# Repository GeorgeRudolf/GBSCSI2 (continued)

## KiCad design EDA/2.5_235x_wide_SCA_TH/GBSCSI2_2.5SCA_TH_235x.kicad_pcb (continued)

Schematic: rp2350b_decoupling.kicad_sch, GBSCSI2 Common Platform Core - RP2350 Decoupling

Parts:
C9, C11, C13, C14, C15, C16, C17, C18, C19, C36, C43: 100nF; C_0402_1005Metric; LCSC C307331
C10: 4.7μF; C_0402_1005Metric; LCSC C23733
C12: 1μF; C_0402_1005Metric; LCSC C52923

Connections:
+1.1V: C9.1, C10.1, C11.1; also elsewhere on the board
+3.3V: C12.1, C13.1, C14.1, C15.1, C16.1, C17.1, C18.1, C19.1, C36.1, C43.1; also elsewhere on the board
GND: C9.2, C10.2, C11.2, C12.2, C13.2, C14.2, C15.2, C16.2, C17.2, C18.2, C19.2, C36.2, C43.2; also elsewhere on the board

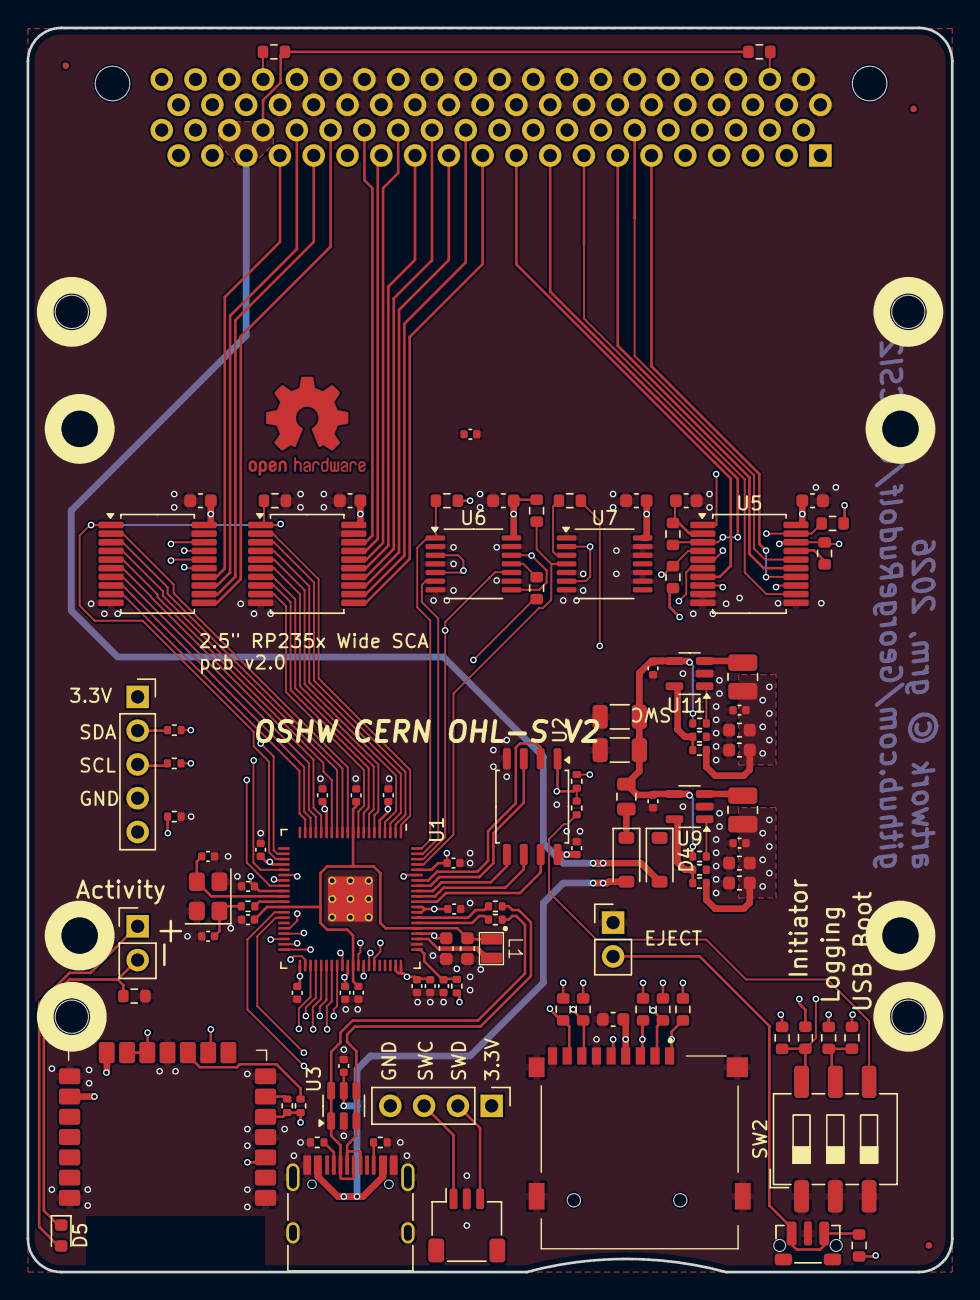
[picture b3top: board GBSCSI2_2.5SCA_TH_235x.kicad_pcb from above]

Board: 4 copper layers, 69.5 x 93.5 mm, 112 parts (1 on the bottom side), 113 nets.

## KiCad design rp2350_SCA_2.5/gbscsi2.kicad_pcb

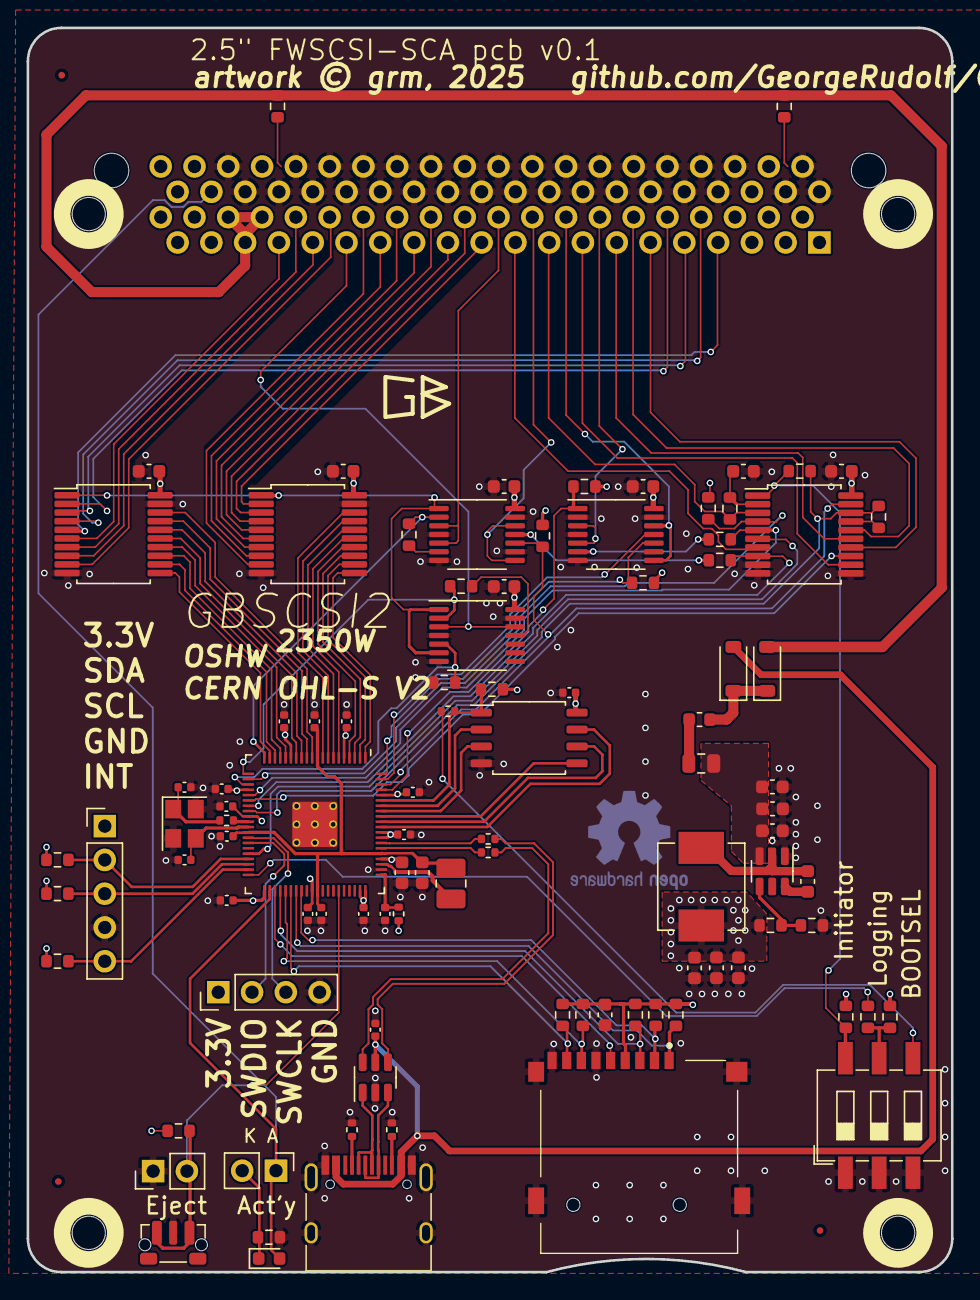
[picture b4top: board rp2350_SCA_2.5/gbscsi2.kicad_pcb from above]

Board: 4 copper layers, 69.5 x 93.6 mm, 105 parts (1 on the bottom side), 113 nets.

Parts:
C1, C15: 10uF; C_0603_1608Metric
C2: 12pF; C_0603_1608Metric
C3, C4, C5, C6, C7, C14, C16, C18, C37: 100nF; C_0603_1608Metric
C12, C13: 22uF; C_0603_1608Metric
C17: 1uF; C_0603_1608Metric
C20, C21: 22pF; C_0402_1005Metric
C22, C24, C27, C28, C29, C30, C31, C32, C33, C34, C38, C39: 100nF; C_0402_1005Metric
C23, C36: 4.7uF; C_0402_1005Metric
C25: 1uF; C_0402_1005Metric
C26, C35: 4.7uF; C_0603_1608Metric
D1: YELLOW; LED_0603_1608Metric
D3, D5: D_Schottky; D_SOD-123
F2: 1A; Fuse_0805_2012Metric
FID1, FID2, FID3: Fiducial; Fiducial_0.5mm_Mask1mm
H1, H2, H3, H4: MH2.5_NPTH
J1: USB_DATA; USB_C_Receptacle_HRO_TYPE-C-31-M-12
J2: TF003; TF01A
J3, J8: Conn_01x02; PinHeader_1x02_P2.54mm_Vertical
J6: Conn_01x05; PinHeader_1x05_P2.54mm_Vertical
J7: Conn_01x04; PinHeader_1x04_P2.54mm_Vertical
J9: Conn_02x40_Counter_Clockwise; CHAMPII_80
L1: Ferrite_Bead_Small; L_0603_1608Metric
L2: 2.2uH; L_Vishay_IHLP-2525
L3: 3.3uH; L_1008_2520Metric_Pad1.43x2.20mm_HandSolder
R1, R2, R3, R5, R7, R8, R9, R10, R11, R12, R13, R15, R40, R51, R52, R54, R66: 4k7; R_0603_1608Metric
R4, R6, R17, R19, R20, R21, R64: 1k; R_0603_1608Metric
R14, R53: 1k; R_0402_1005Metric
R16: 110; R_0603_1608Metric
R18, R42, R67: 10k; R_0603_1608Metric
R41: 31k6; R_0603_1608Metric
R46, R47: 5k1; R_0402_1005Metric
R48, R49, R65: 27; R_0402_1005Metric
R50: 510; R_0603_1608Metric
SW1: SW_DIP_x03; SW_DIP_SPSTx03_Slide_6.7x9.18mm_W8.61mm_P2.54mm_LowProfile
SW2: GT-TC108A-H034-L1S; SW_Push_1P1T-MP_NO_Horizontal_Alps_SKRTLAE010
U1: RP2350_80QFN; RP2350-QFN-80-1EP_10x10_P0.4mm_EP3.4x3.4mm_ThermalVias
U2, U3, U11: 74LVT245; SSOP-20_5.3x7.2mm_P0.65mm
U4, U5, U6: 74LVT125; TSSOP-14_4.4x5mm_P0.65mm
U8: AP62250WU; TSOT-23-6
U9: USB TVS; SOT-23-6
U10: W25Q128JVS; SOIC-8_5.23x5.23mm_P1.27mm
Y1: 12MHz; Crystal_SMD_3225-4Pin_3.2x2.5mm

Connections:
+1V1: C22.1, C23.1, C24.1, C35.1, L3.1, U1.10 (DVDD), U1.32 (DVDD), U1.51 (DVDD), U1.65 (VREG_FB)
+3V3: C1.1, C3.1, C4.1, C5.1, C6.1, C7.1, C12.1, C13.1, C16.1, C25.1, C26.1, C27.1, C28.1, C29.1, C30.1, C31.1, C32.1, C34.1, C37.1, C38.1, C39.1, J2.4 (VDD), J6.1, J7.1, L2.2, R1.2, R2.2, R3.2, R4.1, R5.2, R6.1, R7.2, R11.1, R12.1, R13.1, R15.2, R40.1, R41.1, R51.2, R52.2, R54.2, R65.2, R66.1, U1.5 (IOVDD), U1.15 (IOVDD), U1.24 (IOVDD), U1.29 (IOVDD), U1.41 (IOVDD), U1.50 (IOVDD), U1.59 (ADC_AVDD), U1.60 (IOVDD), U1.64 (VREG_VIN), U1.68 (USB_OTP_VDD), U1.69 (QSPI_IOVDD), U1.76 (IOVDD), U2.20 (VCC), U3.20 (VCC), U4.14 (VCC), U5.14 (VCC), U6.14 (VCC), U10.8 (VCC), U11.20 (VCC)
+5V: C15.1, C17.1, C18.1, F2.2, U8.3 (VIN)
/5V_IN: D3.2 (A), J9.34, J9.35, J9.36, R18.2, R67.2
/5V_TIE: D3.1 (K), D5.1 (K), L1.2
/ACTY: D1.2 (A), J3.1, J9.77, U1.42 (GPIO33)
/ACTY_RTN: D1.1 (K), J3.2, R50.2
/BUS_DIR: R10.2, U1.23 (GPIO23), U4.5
/CC1: J1.A5 (CC1), R47.1
/CC2: J1.B5 (CC2), R46.1
/Din+: J1.A6 (D1+), J1.B6 (D2+), U9.3 (I/O2)
/Din-: J1.A7 (D1-), J1.B7 (D2-), U9.1 (I/O1)
/Dout+: R48.1, U9.4 (I/O2)
/Dout-: R49.1, U9.6 (I/O1)
/EJECT: J8.2, R66.2, SW2.1 (A), U1.55 (GPIO44_ADC4)
/I²C_INT: J6.5, R52.1, U1.39 (GPIO31)
/I²C_SCL: J6.3, R51.1, U1.38 (GPIO30)
/I²C_SDA: J6.2, R15.1, U1.37 (GPIO29)
/QSPI_SCLK: U1.71 (QSPI_SCLK), U10.6 (CLK)
/QSPI_SD0: U1.72 (QSPI_SD0), U10.5 (DI(IO0))
/QSPI_SD1: U1.74 (QSPI_SD1), U10.2 (DO(IO1))
/QSPI_SD2: U1.73 (QSPI_SD2), U10.3 (IO2)
/QSPI_SD3: U1.70 (QSPI_SD3), U10.7 (IO3)
/QSPI_SS: R53.1, R54.1, U1.75 (QSPI_SS), U10.1 (~CS)
/SCSI_I/~O: J9.11, U3.14 (B4)
/SCSI_~ATTN: J9.19, U3.7 (A5)
/SCSI_~C/D: J9.13, U3.15 (B3)
/SCSI_~REQ: J9.12, U3.16 (B2)
/SDIO_CLK: J2.5 (CLK), U1.43 (GPIO34)
/SDIO_CMD: J2.3 (CMD/DI), R3.1, U1.44 (GPIO35)
/SDIO_D0: J2.7 (DAT0/DO), R5.1, U1.45 (GPIO36)
/SDIO_D1: J2.8 (DAT1/NC), R7.1, U1.46 (GPIO37)
/SDIO_D2: J2.1 (DAT2/NC), R1.1, U1.47 (GPIO38)
/SDIO_D3: J2.2 (DAT3/CS), R2.1, U1.48 (GPIO39)
/SWCLK: J7.3, U1.33 (SWCLK)
/SWD: J7.2, U1.34 (SWDIO)
/USB_D+: R48.2, U1.67 (USB_DP)
/USB_D-: R49.2, U1.66 (USB_DM)
/VBUS: C33.1, D5.2 (A), J1.A4 (VBUS), J1.A9 (VBUS), J1.B4 (VBUS), J1.B9 (VBUS), U9.5 (VBUS)
/VREG_LX: L3.2, U1.63 (VREG_LX)
/XIN: R14.1, U1.30 (XIN)
/XOUT: C20.1, U1.31 (XOUT), Y1.3
/~BUS_DIR: U2.1 (A->B), U4.1, U4.6, U5.1, U11.1 (A->B)
/~DEBUG: R9.2, U1.40 (GPIO32)
/~INITIATOR: R4.2, R8.1, SW1.6, U3.1 (A->B)
/~MCU_ACK: R8.2, R17.2, U1.28 (GPIO27), U3.18 (B0)
/~MCU_ATTN: U1.26 (GPIO25), U3.13 (B5)
/~MCU_BSY_OUT: R11.2, U1.78 (GPIO1), U3.19 (CE), U5.10
/~MCU_CD/SEL_IN: R20.1, U1.25 (GPIO24), U3.5 (A3)
/~MCU_IO: U1.36 (GPIO28), U3.6 (A4)
/~MCU_MSG/BSY_IN: R21.1, U1.27 (GPIO26), U3.8 (A6)
/~MCU_REQ: R40.2, U1.22 (GPIO22), U3.4 (A2)
/~MCU_RST_IN: U1.79 (GPIO2), U6.11
/~MCU_RST_OUT: R12.2, U1.80 (GPIO3), U6.10
/~MCU_SD0: U1.1 (GPIO4), U2.11 (B7)
/~MCU_SD1: U1.2 (GPIO5), U2.12 (B6)
/~MCU_SD2: U1.3 (GPIO6), U2.13 (B5)
/~MCU_SD3: U1.4 (GPIO7), U2.14 (B4)
/~MCU_SD4: U1.6 (GPIO8), U2.15 (B3)
/~MCU_SD5: U1.7 (GPIO9), U2.16 (B2)
/~MCU_SD6: U1.8 (GPIO10), U2.17 (B1)
/~MCU_SD7: U1.9 (GPIO11), U2.18 (B0)
/~MCU_SD8: U1.11 (GPIO12), U11.18 (B0)
/~MCU_SD9: U1.12 (GPIO13), U11.17 (B1)
/~MCU_SD10: U1.13 (GPIO14), U11.16 (B2)
/~MCU_SD11: U1.14 (GPIO15), U11.15 (B3)
/~MCU_SD12: U1.16 (GPIO16), U11.14 (B4)
/~MCU_SD13: U1.17 (GPIO17), U11.13 (B5)
/~MCU_SD14: U1.18 (GPIO18), U11.12 (B6)
/~MCU_SD15: U1.19 (GPIO19), U11.11 (B7)
/~MCU_SDP1: R64.2, U1.21 (GPIO21), U4.2
/~MCU_SDP: R19.2, U1.20 (GPIO20), U5.2
/~MCU_SEL_OUT: R13.2, U1.77 (GPIO0), U6.1
/~SCSI_ACK: J9.17, R16.1, U3.3 (A1)
/~SCSI_BSY: J9.18, U5.8, U5.12
/~SCSI_MSG: J9.15, U3.12 (B6)
/~SCSI_RST: J9.16, U6.8, U6.12
/~SCSI_SD0: J9.28, U2.9 (A7)
/~SCSI_SD1: J9.27, U2.8 (A6)
/~SCSI_SD2: J9.26, U2.7 (A5)
/~SCSI_SD3: J9.25, U2.6 (A4)
/~SCSI_SD4: J9.24, U2.5 (A3)
/~SCSI_SD5: J9.23, U2.4 (A2)
/~SCSI_SD6: J9.22, U2.3 (A1)
/~SCSI_SD7: J9.21, U2.2 (A0)
/~SCSI_SD8: J9.10, U11.2 (A0)
/~SCSI_SD9: J9.9, U11.3 (A1)
/~SCSI_SD10: J9.8, U11.4 (A2)
/~SCSI_SD11: J9.7, U11.5 (A3)
/~SCSI_SD12: J9.33, U11.6 (A4)
/~SCSI_SD13: J9.32, U11.7 (A5)
/~SCSI_SD14: J9.31, U11.8 (A6)
/~SCSI_SD15: J9.30, U11.9 (A7)
/~SCSI_SDP1: J9.29, U4.3, U4.12
/~SCSI_SDP: J9.20, U5.3, U5.5
/~SCSI_SEL: J9.14, U6.3, U6.5
/~USB_BOOT: R53.2, SW1.4
GND: C1.2, C2.2, C3.2, C4.2, C5.2, C6.2, C7.2, C12.2, C13.2, C15.2, C16.2, C17.2, C18.2, C20.2, C21.2, C22.2, C23.2, C24.2, C25.2, C26.2, C27.2, C28.2, C29.2, C30.2, C31.2, C32.2, C33.2, C34.2, C35.2, C36.2, C37.2, C38.2, C39.2, J1.A1 (GND), J1.A12 (GND), J1.B1 (GND), J1.B12 (GND), J1.S1 (SHIELD), J2.6 (GND), J2.CD1, J2.MP1, J2.MP2, J2.MP3, J2.MP4, J6.4, J7.4, J8.1, J9.41, J9.42, J9.43, J9.46, J9.47, J9.48, J9.49, J9.50, J9.51, J9.52, J9.53, J9.54, J9.55, J9.56, J9.57, J9.58, J9.59, J9.60, J9.61, J9.62, J9.63, J9.64, J9.65, J9.66, J9.67, J9.68, J9.69, J9.70, J9.71, J9.72, J9.73, J9.75, J9.76, R10.1, R42.2, R46.2, R47.2, R50.1, SW1.1, SW1.2, SW1.3, SW2.2 (B), U1.62 (VREG_PGND), U1.81 (GND), U2.10 (GND), U2.19 (CE), U3.9 (A7), U3.10 (GND), U3.11 (B7), U4.4, U4.7 (GND), U4.13, U5.4, U5.7 (GND), U5.9, U5.13, U6.2, U6.4, U6.7 (GND), U6.9, U6.13, U8.1 (GND), U9.2 (GND), U10.4 (GND), U11.10 (GND), U11.19 (CE), Y1.2, Y1.4
unnamed: C21.1, R14.2, Y1.1
unnamed: F2.1, L1.1
unnamed: J9.44, R67.1
unnamed: J9.74, R18.1
unnamed: R6.2, R9.1, SW1.5
unnamed: R19.1, U5.6
unnamed: R20.2, U6.6
unnamed: R21.2, U5.11
unnamed: R64.1, U4.11
unnamed: C36.1, R65.1, U1.61 (VREG_AVDD)
unnamed: C2.1, R16.2, U3.2 (A0)
unnamed: R17.1, U3.17 (B1)
unnamed: C14.2, U8.6 (BST)
unnamed: R41.2, R42.1, U8.4 (FB)
unnamed: C14.1, L2.1, U8.2 (SW)

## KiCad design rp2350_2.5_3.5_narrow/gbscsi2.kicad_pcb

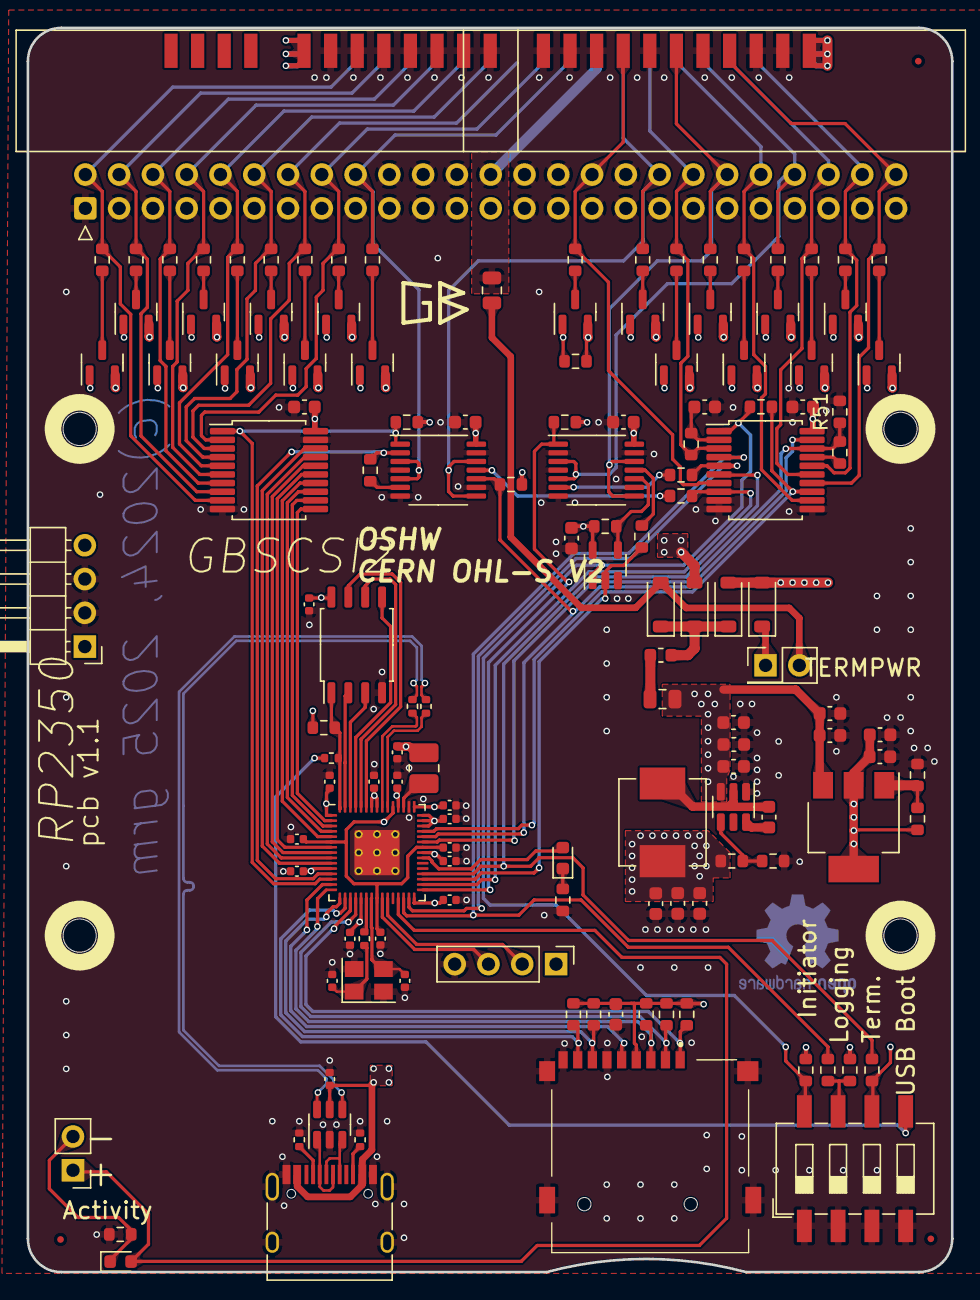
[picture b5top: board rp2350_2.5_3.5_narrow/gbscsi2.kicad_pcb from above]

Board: 4 copper layers, 69.5 x 93.5 mm, 144 parts (0 on the bottom side), 112 nets.

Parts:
C1, C15: 10uF; C_0603_1608Metric
C2: 12pF; C_0603_1608Metric
C3, C4, C5, C6, C7, C10, C11, C14, C16, C18: 100nF; C_0603_1608Metric
C8, C9, C17: 1uF; C_0603_1608Metric
C12, C13: 22uF; C_0603_1608Metric
C20, C21: 22pF; C_0402_1005Metric
C22, C24, C27, C28, C29, C30, C31, C32, C33, C34: 100nF; C_0402_1005Metric
C23, C25: 1uF; C_0402_1005Metric
C26, C35: 4.7uF; C_0402_1005Metric
C36: 100n; C_0402_1005Metric
D1, D6: YELLOW; LED_0603_1608Metric
D2, D3, D4, D5: D_Schottky; D_SOD-123
F1, F2: 1A; Fuse_0805_2012Metric
FID1, FID2, FID3: Fiducial; Fiducial_0.5mm_Mask1mm
H1, H2, H3, H4: MH2.5_NPTH
J1: USB_DATA; USB_C_Receptacle_HRO_TYPE-C-31-M-12
J2: TF003; TF01A
J3: Conn_01x02; PinHeader_1x02_P2.54mm_Vertical
J4: Conn_01x04; PinHeader_1x04_P2.54mm_Horizontal
J5: SCSI_50-2P_2mm; PinHeader_2x25-2_P2.00mm_straddle
J6: SCSI_50P_2.54mm; IDC-Header_2x25_P2.54mm_Horizontal
J7: Conn_01x04; PinHeader_1x04_P2.54mm_Vertical
JP3: Jumper_2_Open; PinHeader_2x01_P2.54mm_Vertical
L1: Ferrite_Bead_Small; L_0603_1608Metric
L2: 2.2uH; L_Vishay_IHLP-2525
L3: 3.3uH; L_1008_2520Metric_Pad1.43x2.20mm_HandSolder
Q1, Q2, Q3, Q4, Q5, Q6, Q7, Q8, Q9, Q10, Q11, Q12, Q13, Q14, Q15, Q16, Q17, Q18: AO3401A; SOT-23
R1, R2, R3, R5, R7, R8, R9, R10, R11, R12, R13, R18, R40, R43, R54: 4k7; R_0603_1608Metric
R4, R6, R17, R19, R20, R21, R51: 1k; R_0603_1608Metric
R14, R53: 1k; R_0402_1005Metric
R16, R22, R23, R24, R25, R26, R27, R28, R29, R30, R31, R32, R33, R34, R35, R36, R37, R38, R39: 110; R_0603_1608Metric
R41: 31k6; R_0603_1608Metric
R42: 10k; R_0603_1608Metric
R44: R_0603_1608Metric
R45: 0; R_0603_1608Metric
R46, R47: 5k1; R_0402_1005Metric
R48, R49: 27; R_0402_1005Metric
R50, R52: 510; R_0603_1608Metric
SW1: SW_DIP_x04; SW_DIP_SPSTx04_Slide_6.7x11.72mm_W8.61mm_P2.54mm_LowProfile
U1: RP2350_60QFN; RP2350-QFN-60-1EP_7x7_P0.4mm_EP3.4x3.4mm_ThermalVias
U2, U3: 74LVT245; SSOP-20_5.3x7.2mm_P0.65mm
U4: 74AHCT1G125; SOT-23-5
U5, U6: 74LVT125; TSSOP-14_4.4x5mm_P0.65mm
U7: AZ1117-2.85; SOT-223-3_TabPin2
U8: AP62250WU; TSOT-23-6
U9: USB TVS; SOT-23-6
U10: W25Q128JVS; SOIC-8_5.23x5.23mm_P1.27mm
Y1: 12MHz; Crystal_SMD_3225-4Pin_3.2x2.5mm

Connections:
+1V1: C22.1, C23.1, C24.1, C35.1, L3.1, U1.6 (DVDD), U1.23 (DVDD), U1.39 (DVDD), U1.50 (VREG_FB)
+2V8: C9.1, C11.1, Q1.2 (S), Q2.2 (S), Q3.2 (S), Q4.2 (S), Q5.2 (S), Q6.2 (S), Q7.2 (S), Q8.2 (S), Q9.2 (S), Q10.2 (S), Q11.2 (S), Q12.2 (S), Q13.2 (S), Q14.2 (S), Q15.2 (S), Q16.2 (S), Q17.2 (S), Q18.2 (S), R40.1, R44.2, U7.2 (VO)
+3V3: C1.1, C3.1, C4.1, C5.1, C6.1, C7.1, C12.1, C13.1, C16.1, C25.1, C26.1, C27.1, C28.1, C29.1, C30.1, C31.1, C32.1, C34.1, C36.1, J2.4 (VDD), J7.1, L2.2, R1.2, R2.2, R3.2, R4.1, R5.2, R6.1, R7.2, R10.1, R11.1, R12.1, R13.1, R41.1, R54.2, U1.1 (IOVDD), U1.11 (IOVDD), U1.20 (IOVDD), U1.30 (IOVDD), U1.38 (IOVDD), U1.43 (GPIO29_ADC3), U1.44 (ADC_AVDD), U1.45 (IOVDD), U1.46 (VREG_AVDD), U1.49 (VREG_VIN), U1.53 (USB_OTP_VDD), U1.54 (QSPI_IOVDD), U2.20 (VCC), U3.20 (VCC), U4.5 (VCC), U5.14 (VCC), U6.14 (VCC), U10.8 (VCC)
+5V: C8.1, C10.1, C15.1, C17.1, C18.1, F2.2, U7.3 (VI), U8.3 (VIN)
/5V_IN: D2.2 (A), D3.2 (A), J4.1, J5.1, J5.2, J5.39, J5.40
/5V_TIE: D3.1 (K), D4.1 (K), D5.1 (K), L1.2
/ACTY: D1.1 (K), J3.2, R50.2
/CC1: J1.A5 (CC1), R47.1
/CC2: J1.B5 (CC2), R46.1
/Din+: J1.A6 (D1+), J1.B6 (D2+), U9.3 (I/O2)
/Din-: J1.A7 (D1-), J1.B7 (D2-), U9.1 (I/O1)
/Dout+: R48.1, U9.4 (I/O2)
/Dout-: R49.1, U9.6 (I/O1)
/GPIO16: D1.2 (A), J3.1, U1.27 (GPIO16)
/MCU_RST: R18.2, U1.33 (GPIO21), U4.2
/QSPI_SCLK: U1.56 (QSPI_SCLK), U10.6 (CLK)
/QSPI_SD0: U1.57 (QSPI_SD0), U10.5 (DI(IO0))
/QSPI_SD1: U1.59 (QSPI_SD1), U10.2 (DO(IO1))
/QSPI_SD2: U1.58 (QSPI_SD2), U10.3 (IO2)
/QSPI_SD3: U1.55 (QSPI_SD3), U10.7 (IO3)
/QSPI_SS: R53.1, R54.1, U1.60 (QSPI_SS), U10.1 (~CS)
/SCSI_I/~O: J5.33, J6.50, R39.1, U3.14 (B4)
/SCSI_~ATTN: J5.25, J6.32, R31.1, U3.7 (A5)
/SCSI_~C/D: J5.34, J6.46, R37.1, U3.15 (B3)
/SCSI_~REQ: J5.36, J6.48, R38.1, U3.16 (B2)
/SDIO_CLK: J2.5 (CLK), U1.14 (GPIO10)
/SDIO_CMD: J2.3 (CMD/DI), R3.1, U1.15 (GPIO11)
/SDIO_D0: J2.7 (DAT0/DO), R5.1, U1.16 (GPIO12)
/SDIO_D1: J2.8 (DAT1/NC), R7.1, U1.17 (GPIO13)
/SDIO_D2: J2.1 (DAT2/NC), R1.1, U1.18 (GPIO14)
/SDIO_D3: J2.2 (DAT3/CS), R2.1, U1.19 (GPIO15)
/SWCLK: J7.3, U1.24 (SWCLK)
/SWD: J7.2, U1.25 (SWD)
/TERMPWR: F1.1, J5.24, J6.26
/USB_D+: R48.2, U1.52 (USB_DP)
/USB_D-: R49.2, U1.51 (USB_DM)
/VBUS: C33.1, D5.2 (A), J1.A4 (VBUS), J1.A9 (VBUS), J1.B4 (VBUS), J1.B9 (VBUS), U9.5 (VBUS)
/VREG_LX: L3.2, U1.48 (VREG_LX)
/XIN: R14.1, U1.21 (XIN)
/XOUT: C20.1, U1.22 (XOUT), Y1.3
/~BUS_DIR: R10.2, U1.13 (GPIO9), U2.1 (A->B), U5.1
/~DEBUG: R6.2, R9.1, SW1.7
/~INITIATOR: R4.2, R8.1, SW1.8, U3.1 (A->B), U4.1
/~MCU_ACK: R17.2, R51.1, U1.40 (GPIO26_ADC0), U3.18 (B0)
/~MCU_ATTN: R8.2, U1.42 (GPIO28_ADC2), U3.13 (B5)
/~MCU_BSY_OUT: R11.2, U1.41 (GPIO27_ADC1), U3.19 (CE), U5.10
/~MCU_CD/SEL_IN: R20.1, U1.29 (GPIO18), U3.5 (A3)
/~MCU_IO: R43.2, U1.34 (GPIO22), U3.6 (A4)
/~MCU_MSG/BSY_IN: R21.1, U1.32 (GPIO20), U3.8 (A6)
/~MCU_REQ: R9.2, U1.28 (GPIO17), U3.4 (A2)
/~MCU_SD0: U1.2 (GPIO0), U2.11 (B7)
/~MCU_SD1: U1.3 (GPIO1), U2.12 (B6)
/~MCU_SD2: U1.4 (GPIO2), U2.13 (B5)
/~MCU_SD3: U1.5 (GPIO3), U2.14 (B4)
/~MCU_SD4: U1.7 (GPIO4), U2.15 (B3)
/~MCU_SD5: U1.8 (GPIO5), U2.16 (B2)
/~MCU_SD6: U1.9 (GPIO6), U2.17 (B1)
/~MCU_SD7: U1.10 (GPIO7), U2.18 (B0)
/~MCU_SDP: R19.2, U1.12 (GPIO8), U5.2
/~MCU_SEL_OUT: R13.2, U1.31 (GPIO19), U6.1
/~RST_OUT: R12.2, U4.4, U6.10
/~SCSI_ACK: J5.28, J6.38, R16.1, R33.1, U3.3 (A1)
/~SCSI_BSY: J5.26, J6.36, R32.1, U5.8, U5.12
/~SCSI_MSG: J5.30, J6.42, R35.1, U3.12 (B6)
/~SCSI_RST: J5.29, J6.40, R34.1, U6.8, U6.12
/~SCSI_SD0: J5.6, J6.2, R22.1, U2.9 (A7)
/~SCSI_SD1: J5.8, J6.4, R23.1, U2.8 (A6)
/~SCSI_SD2: J5.10, J6.6, R24.1, U2.7 (A5)
/~SCSI_SD3: J5.12, J6.8, R25.1, U2.6 (A4)
/~SCSI_SD4: J5.14, J6.10, R26.1, U2.5 (A3)
/~SCSI_SD5: J5.16, J6.12, R27.1, U2.4 (A2)
/~SCSI_SD6: J5.18, J6.14, R28.1, U2.3 (A1)
/~SCSI_SD7: J5.20, J6.16, R29.1, U2.2 (A0)
/~SCSI_SDP: J5.22, J6.18, R30.1, U5.3, U5.5
/~SCSI_SEL: J5.32, J6.44, R36.1, U6.3, U6.5
/~TERM_EN: Q1.1 (G), Q2.1 (G), Q3.1 (G), Q4.1 (G), Q5.1 (G), Q6.1 (G), Q7.1 (G), Q8.1 (G), Q9.1 (G), Q10.1 (G), Q11.1 (G), Q12.1 (G), Q13.1 (G), Q14.1 (G), Q15.1 (G), Q16.1 (G), Q17.1 (G), Q18.1 (G), R40.2, R43.1, SW1.6
/~USB_BOOT: R53.2, SW1.5
GND: C1.2, C2.2, C3.2, C4.2, C5.2, C6.2, C7.2, C8.2, C9.2, C10.2, C11.2, C12.2, C13.2, C15.2, C16.2, C17.2, C18.2, C20.2, C21.2, C22.2, C23.2, C24.2, C25.2, C26.2, C27.2, C28.2, C29.2, C30.2, C31.2, C32.2, C33.2, C34.2, C35.2, C36.2, J1.A1 (GND), J1.A12 (GND), J1.B1 (GND), J1.B12 (GND), J1.S1 (SHIELD), J2.6 (GND), J2.CD1, J2.MP1, J2.MP2, J2.MP3, J2.MP4, J4.2, J4.3, J5.3, J5.4, J5.5, J5.7, J5.9, J5.11, J5.13, J5.15, J5.19, J5.21, J5.23, J5.27, J5.31, J5.35, J5.37, J5.38, J6.1, J6.3, J6.5, J6.7, J6.9, J6.11, J6.13, J6.15, J6.17, J6.19, J6.20, J6.21, J6.22, J6.23, J6.24, J6.25, J6.27, J6.28, J6.29, J6.30, J6.31, J6.33, J6.34, J6.35, J6.37, J6.39, J6.41, J6.43, J6.45, J6.47, J6.49, J7.4, R42.2, R45.1, R46.2, R47.2, R50.1, R51.2, R52.1, SW1.1, SW1.2, SW1.3, SW1.4, U1.47 (VREG_PGND), U1.61 (GND), U2.10 (GND), U2.19 (CE), U3.9 (A7), U3.10 (GND), U3.11 (B7), U4.3 (GND), U5.4, U5.7 (GND), U5.9, U5.13, U6.2, U6.4, U6.7 (GND), U6.9, U6.13, U8.1 (GND), U9.2 (GND), U10.4 (GND), Y1.2, Y1.4
unnamed: C21.1, R14.2, Y1.1
unnamed: D2.1 (K), JP3.1 (A)
unnamed: D4.2 (A), F1.2, JP3.2 (B)
unnamed: D6.2 (A), U1.37 (GPIO25)
unnamed: D6.1 (K), R52.2
unnamed: F2.1, L1.1
unnamed: Q1.3 (D), R22.2
unnamed: Q2.3 (D), R23.2
unnamed: Q3.3 (D), R24.2
unnamed: Q4.3 (D), R25.2
unnamed: Q5.3 (D), R26.2
unnamed: Q6.3 (D), R27.2
unnamed: Q7.3 (D), R28.2
unnamed: Q8.3 (D), R29.2
unnamed: Q9.3 (D), R30.2
unnamed: Q10.3 (D), R31.2
unnamed: Q11.3 (D), R32.2
unnamed: Q12.3 (D), R33.2
unnamed: Q13.3 (D), R34.2
unnamed: Q14.3 (D), R35.2
unnamed: Q15.3 (D), R36.2
unnamed: Q16.3 (D), R37.2
unnamed: Q17.3 (D), R38.2
unnamed: Q18.3 (D), R39.2
unnamed: R18.1, U6.11
unnamed: R19.1, U5.6
unnamed: R20.2, U6.6
unnamed: R21.2, U5.11
unnamed: C2.1, R16.2, U3.2 (A0)
unnamed: R17.1, U3.17 (B1)
unnamed: R44.1, R45.2, U7.1 (GND)
unnamed: C14.2, U8.6 (BST)
unnamed: R41.2, R42.1, U8.4 (FB)
unnamed: C14.1, L2.1, U8.2 (SW)

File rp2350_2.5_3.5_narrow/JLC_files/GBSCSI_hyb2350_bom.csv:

Designator,Footprint,Quantity,Value,LCSC Part #
"C1, C10, C11, C14, C16, C18, C3, C4, C5, C6, C7",603,11,100nF,C14663
"C12, C13",603,2,22uF,C59461
C15,603,1,10uF,C96446
"C17, C8, C9",603,3,1uF,C15849
C2,603,1,12pF,C38523
"C20, C21",402,2,22pF,C1555
"C22, C24, C27, C28, C29, C30, C31, C32, C33, C34",402,10,100nF,C307331
"C23, C25",402,2,1uF,C52923
"C26, C35",402,2,4.7uF,
C36,402,1,100n,
"D1, D6",603,2,YELLOW,C72038
"D2, D3, D4, D5",D_SOD-123,4,D_Schottky,C82544
"F1, F2",805,2,1A,C468888
FID1,Fiducial_0.5mm_Mask1mm,1,Fiducial,N/A
J1,USB_C_Receptacle_HRO_TYPE-C-31-M-12,1,USB_DATA,C165948
J2,TF01A,1,TF003,C5155563 
J3,PinHeader_1x02_P2.54mm_Vertical,1,Conn_01x02,N/A
J4,PinHeader_1x04_P2.54mm_Horizontal,1,Conn_01x04,N/A
J5,PinHeader_2x25-2_P2.00mm_straddle,1,SCSI_50-2P_2mm,N/A
J6,IDC-Header_2x25_P2.54mm_Horizontal,1,SCSI_50P_2.54mm,N/A
J7,PinHeader_1x04_P2.54mm_Vertical,1,Conn_01x04,N/A
JP3,PinHeader_2x01_P2.54mm_Vertical,1,Jumper_2_Open,N/A
L1,603,1,Ferrite_Bead_Small,C1002
L2,L_Vishay_IHLP-2525,1,2.2uH,C540967
L3,1008,1,3.3uH,C222831
"Q1, Q10, Q11, Q12, Q13, Q14, Q15, Q16, Q17, Q18, Q2, Q3, Q4, Q5, Q6, Q7, Q8, Q9",SOT-23,18,AO3401A,C15127
"R1, R10, R11, R12, R13, R18, R2, R3, R40, R43, R5, R54, R7, R8, R9",603,15,4k7,C23162
"R14, R53",402,2,1k,C11702
"R16, R22, R23, R24, R25, R26, R27, R28, R29, R30, R31, R32, R33, R34, R35, R36, R37, R38, R39",603,19,110,C22781
"R17, R19, R20, R21, R4, R51, R6",603,7,1k,C21190
R41,603,1,31k6,C25967
R42,603,1,10k,C25804
R45,603,1,0,C21189
"R46, R47",402,2,5k1,C25905
"R48, R49",402,2,27,C25092
"R50, R52",603,2,510,C23193
SW1,SW_DIP_SPSTx04_Slide_6.7x11.72mm_W8.61mm_P2.54mm_LowProfile,1,SW_DIP_x04,C5160841
U1,RP2350-QFN-60-1EP_7x7_P0.4mm_EP3.4x3.4mm_ThermalVias,1,RP2350_60QFN,C9900136995
U10,SOIC-8_5.23x5.23mm_P1.27mm,1,W25Q128JVS,C97521
"U2, U3",SSOP-20_5.3x7.2mm_P0.65mm,2,74LVT245,C2652121
U4,SOT-23-5,1,74AHCT1G125,C12494
"U5, U6",TSSOP-14_4.4x5mm_P0.65mm,2,74LVT125,C7042
U7,SOT-223-3_TabPin2,1,AZ1117-2.85,C14791
U8,TSOT-23-6,1,AP62250WU,C5184228
U9,SOT-23-6,1,USB TVS,C2827654
Y1,Crystal_SMD_3225-4Pin_3.2x2.5mm,1,12MHz,C133334

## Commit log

2024-03-27 Initial file addition
2024-03-27 Added instructions
2024-04-06 Added Pico populating info
2024-04-23 Corrected wrong keying on 2.5" connector
2024-04-23 Update README.md
    After much fumbling, it's finally right.
2024-08-08 added WIP RP2350 variant
2024-08-30 Changed diodes in BoM, minor corrections to PCB, documentation
2024-10-04 BoM fixes for discrete variants, interactive BoMs added to each major type, mfg files for 2350
2024-10-04 Corrected U9 rotation
2024-10-27 moving RP2350 to full release
2024-10-27 I screwed up the readme, lol
2024-12-13 Added FreeCAD version of drive tray and updated readme to relect purchasing from Emmy Bear Retro's tindie
2025-02-15 Added jank FWSCSI variant
    Just a test board.
2025-03-09 Redoing Wide variant - WIP
2025-03-09 Added SCA variant
2025-03-09 Re-sorting things around
2025-03-09 Attempting to organize sheet details, adding eject buttons to Wide variants
2025-03-10 Cleaning up, updating docs
2025-03-16 Minor BoM fixes, added left-behind HD68 variant eject switch
2026-01-20 Update README.md to clarify project status
    This repo needs a lot of cleanup, too.
2026-01-20 Split basic documentation into separate files
2026-01-20 Added warnings to WIP/incomplete versions
2026-02-04 Archiving old versions, migrating project to fresh redesign - WIP
    See readme. Premade assembly files for new versions not yet available. BoM and DRC still need some fettling.
2026-02-04 Started work on thru-hole SCA wide variant
2026-02-04 Fixing up schematics for SCA before layout
2026-02-04 SCA variant mostly laid out
    Or rather, a first pass.
2026-02-08 Tidying up PCB footprint slightly, more work needed, ERC passes on narrow variants
2026-02-08 Prettifying models
2026-02-09 Fixing PCB footprint
2026-02-23 Update README.md
    Discontinuing development.
2026-05-11 Revert "Update README.md"
    This reverts commit f0003f0886b115c359bf428fdda49687c7eec7d3.
2026-05-11 Resuming work
2026-05-12 Minor tweaks
